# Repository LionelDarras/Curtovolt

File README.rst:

CURTOVOLT
=========

CurToVolt est un projet de développement d'une carte électronique permettant de convertir 4 courants en tensions
pouvant être connectées à un convertisseur Analogique/Numérique pour visualiser ou enregistrer les mesures.

Documentation
-------------

Voir documentation dans le fichier CURTOVOLT-FR.pdf

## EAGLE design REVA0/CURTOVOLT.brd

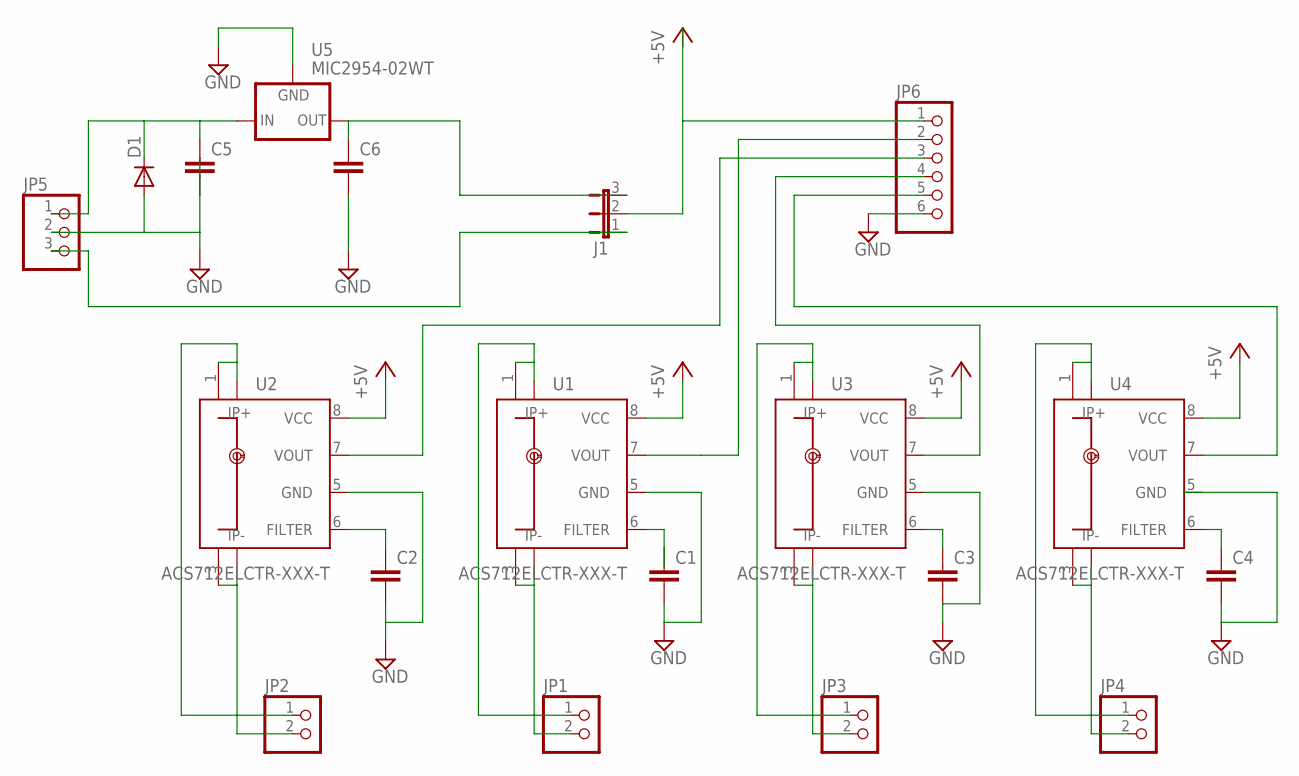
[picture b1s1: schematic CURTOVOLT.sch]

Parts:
C1, C2, C3, C4, C5, C6: C-EUC1206; C1206
D1: DIODE-DO-214AC; DO-214AC
J1: JP2E; JP2
JP1, JP2, JP3, JP4: PINHD-1X2/5MM; 1X02/5MM
JP5: PINHD-1X3/3.5MM; 1X03/3.5MM
JP6: PINHD-1X6/3.5MM; 1X06/3.5MM
U1, U2, U3, U4: ACS712ELCTR-XXX-T; SO8
U5: MIC2954-02WT; TO220V

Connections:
+5V: J1.2, JP6.1, U1.8 (VCC), U2.8 (VCC), U3.8 (VCC), U4.8 (VCC)
GND: C1.2, C2.2, C3.2, C4.2, C5.2, C6.2, D1.A, JP5.2, JP6.6, U1.5 (GND), U2.5 (GND), U3.5 (GND), U4.5 (GND), U5.2 (GND)
unnamed: C2.1, U2.6 (FILTER)
unnamed: C1.1, U1.6 (FILTER)
unnamed: C3.1, U3.6 (FILTER)
unnamed: C4.1, U4.6 (FILTER)
unnamed: C5.1, D1.C, JP5.1, U5.1 (IN)
unnamed: J1.1, JP5.3
unnamed: C6.1, J1.3, U5.3 (OUT)
unnamed: JP6.3, U2.7 (VOUT)
unnamed: JP6.2, U1.7 (VOUT)
unnamed: JP6.4, U3.7 (VOUT)
unnamed: JP6.5, U4.7 (VOUT)
unnamed: JP2.2, U2.3 (IP-), U2.4 (IP-1)
unnamed: JP2.1, U2.1 (IP+), U2.2 (IP+1)
unnamed: JP1.1, U1.1 (IP+), U1.2 (IP+1)
unnamed: JP1.2, U1.3 (IP-), U1.4 (IP-1)
unnamed: JP3.1, U3.1 (IP+), U3.2 (IP+1)
unnamed: JP3.2, U3.3 (IP-), U3.4 (IP-1)
unnamed: JP4.1, U4.1 (IP+), U4.2 (IP+1)
unnamed: JP4.2, U4.3 (IP-), U4.4 (IP-1)

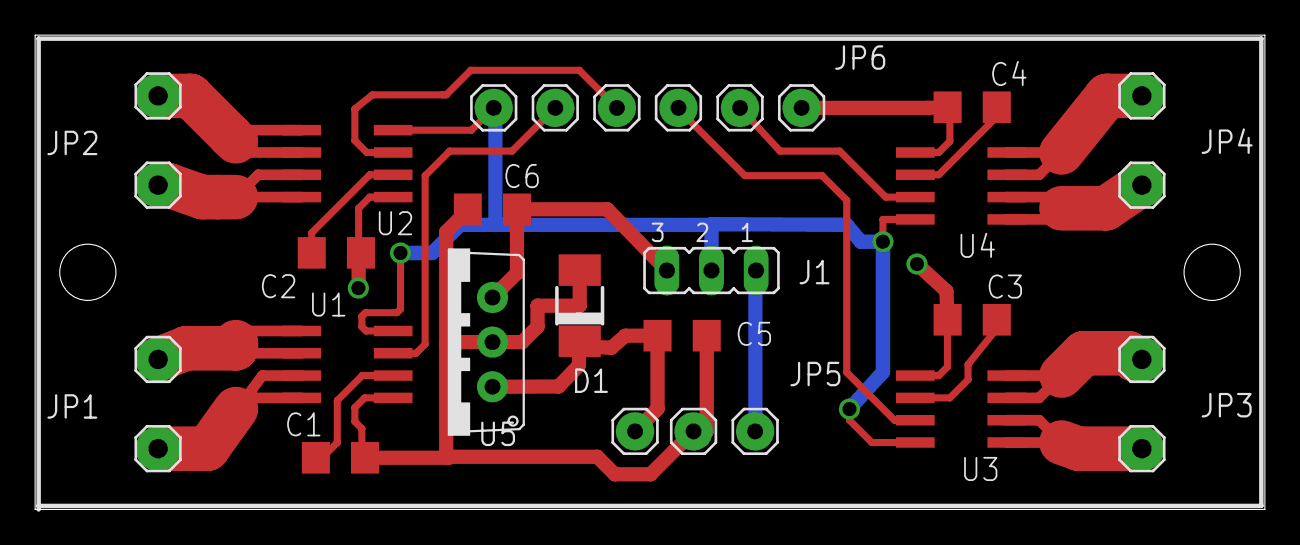
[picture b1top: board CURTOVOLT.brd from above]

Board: 2 copper layers, 70.0 x 27.0 mm, 20 parts (0 on the bottom side), 21 nets.

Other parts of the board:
U$1: ISTERRE-3

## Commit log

2017-06-26 :neckbeard: Added .gitattributes & .gitignore files
2017-07-05 projet initial
